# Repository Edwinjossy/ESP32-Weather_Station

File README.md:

# ESP32 WeatherStation 
This project aims to build a weather station board for recording and uploading common weather data. The measured data can be uploaded to WUnderground or stored and displayed on a dashboard using a local Thingsboard server.

The custom PCB board is designed to work as a shield for the [ESP32 Dev board](https://www.az-delivery.de/it/products/esp32-developmentboard).

As an exercise, no external libraries are used to communicate with the sensors. All drivers are written from scratch. The framework used is ESP-IDF.

[Wunderground Page](https://www.wunderground.com/dashboard/pws/IBARON16/)

## Requirements
 - ESP32 Dev board 
 - Sparkfun Weather Meters
 - SHT31 Temperature/Humidty sensors
 - Custom PCB Weather Board
 - Wunderground API Key
 - ThingsBoard server local/cloud

## Getting started
- Set your WiFi credentials in "lib/Wifi/wifi.h"
- Signup on [Wunderground](https://www.wunderground.com/member/devices) and create a PWS.
- Configure a local installation of [Thingsboard](https://thingsboard.io/) or use their [Cloud](https://thingsboard.cloud/) service.
- Set WUnderground and Thingsboard API  in "lib/Cloud/cloud.h"

## Demo Dashboard
[Salerno, Italy](https://bit.ly/3zLmFFb)

[
](https://bit.ly/3zLmFFb)

## Hardware[EXPERIMENTAL]

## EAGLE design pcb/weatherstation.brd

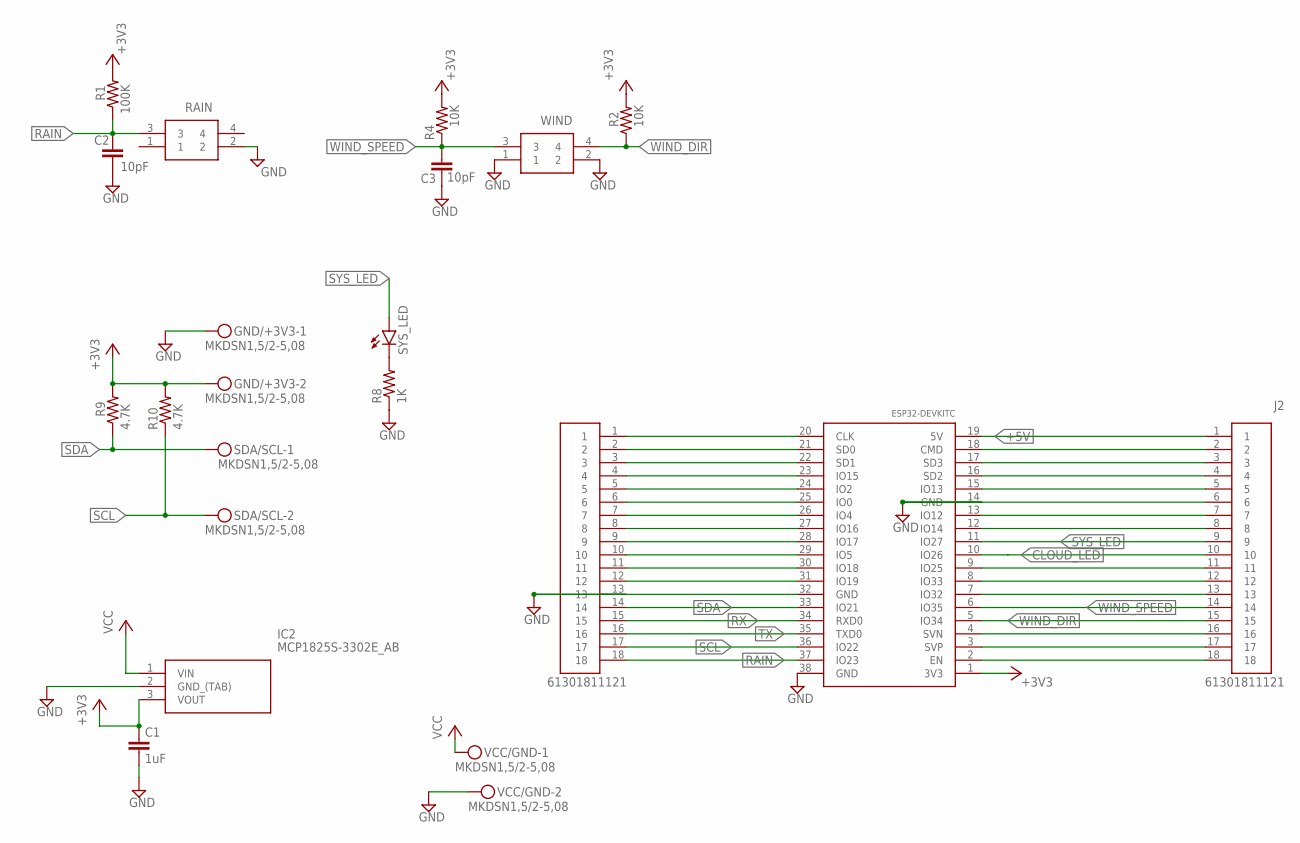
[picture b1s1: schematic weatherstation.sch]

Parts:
C1: 1uF; C025-025X050
C2, C3: 10pF; C025-025X050
GND/+3V3: MKDSN1,5/2-5,08
IC2: MCP1825S-3302E_AB; TO254P482X1024X3124-3P
J1, J2: 61301811121
R1: 100K; 0204/7
R2, R4: 10K; 0204/7
R8: 1K; 0204/7
R9, R10: 4.7K; 0204/7
RAIN: TM5RU1-64_50_; TM5RU16450
SDA/SCL: MKDSN1,5/2-5,08
SYS_LED: LED5MM
U$1: ESP32DEVKITC; ESP32-DEVKITC
VCC/GND: MKDSN1,5/2-5,08
WIND: TM5RU1-64_50_; TM5RU16450

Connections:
+3V3: C1.1, GND/+3V3.2, IC2.3 (VOUT), R1.2, R2.2, R4.2, R9.2, R10.2, U$1.1 (3V3)
+5V: J2.1, U$1.19 (5V)
CLOUD_LED: J2.10, U$1.10 (IO26)
GND: C1.2, C2.2, C3.2, GND/+3V3.1, IC2.2 (GND_(TAB)), J1.13, J2.6, R8.1, RAIN.2, U$1.14 (GND), U$1.32 (GND), U$1.38 (GND), VCC/GND.2, WIND.1, WIND.2
unnamed: J1.1, U$1.20 (CLK)
unnamed: J1.2, U$1.21 (SD0)
unnamed: J1.3, U$1.22 (SD1)
unnamed: J1.4, U$1.23 (IO15)
unnamed: J1.5, U$1.24 (IO2)
unnamed: R8.2, SYS_LED.K (C)
unnamed: J1.6, U$1.25 (IO0)
unnamed: J1.7, U$1.26 (IO4)
unnamed: J1.8, U$1.27 (IO16)
unnamed: J1.9, U$1.28 (IO17)
unnamed: J1.10, U$1.29 (IO5)
unnamed: J1.11, U$1.30 (IO18)
unnamed: J1.12, U$1.31 (IO19)
unnamed: J2.2, U$1.18 (CMD)
unnamed: J2.3, U$1.17 (SD3)
unnamed: J2.4, U$1.16 (SD2)
unnamed: J2.5, U$1.15 (IO13)
unnamed: J2.7, U$1.13 (IO12)
unnamed: J2.8, U$1.12 (IO14)
unnamed: J2.11, U$1.9 (IO25)
unnamed: J2.12, U$1.8 (IO33)
unnamed: J2.13, U$1.7 (IO32)
unnamed: J2.16, U$1.4 (SVN)
unnamed: J2.17, U$1.3 (SVP)
unnamed: J2.18, U$1.2 (EN)
RAIN: C2.1, J1.18, R1.1, RAIN.3, U$1.37 (IO23)
RX: J1.15, U$1.34 (RXD0)
SCL: J1.17, R10.1, SDA/SCL.2, U$1.36 (IO22)
SDA: J1.14, R9.1, SDA/SCL.1, U$1.33 (IO21)
SYS_LED: J2.9, SYS_LED.A, U$1.11 (IO27)
TX: J1.16, U$1.35 (TXD0)
VCC: IC2.1 (VIN), VCC/GND.1
WIND_DIR: J2.15, R2.1, U$1.5 (IO34), WIND.4
WIND_SPEED: C3.1, J2.14, R4.1, U$1.6 (IO35), WIND.3

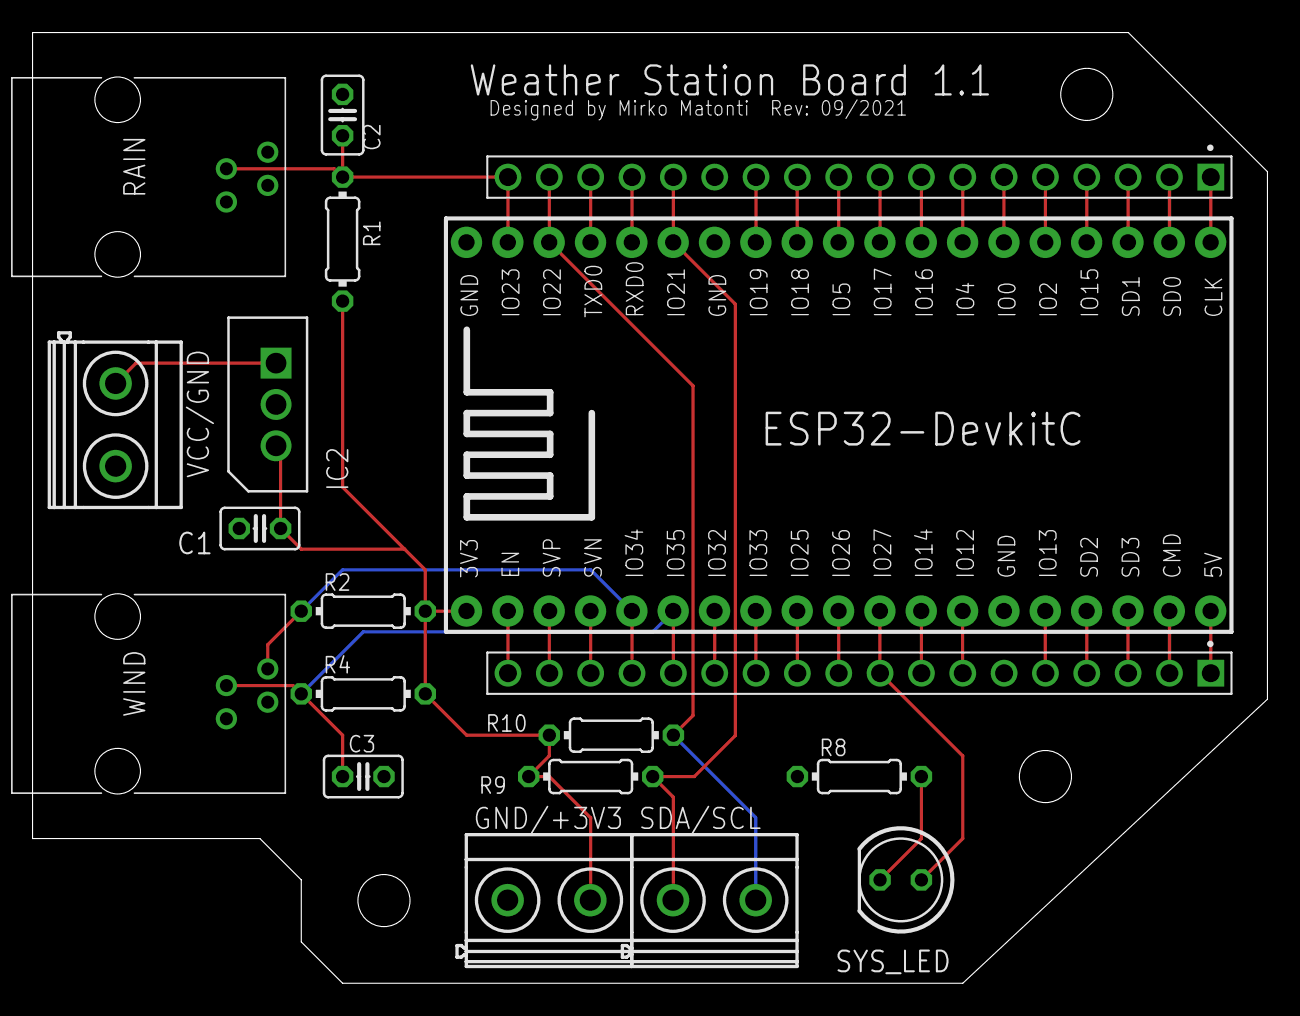
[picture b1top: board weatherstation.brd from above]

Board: 2 copper layers, 75.9 x 58.4 mm, 19 parts (0 on the bottom side), 38 nets.
